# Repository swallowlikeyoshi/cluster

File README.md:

# HEVEN Cluster 펌웨어

**2026 영광 대회 · 계기 클러스터(Instrument Cluster)** — ESP32가 CAN/BLE로 차량 상태(속도·전압·SOC·온도·에러)를 **받아서** LCD에 표현하고, 계기판 버튼 입력을 VCU로 보냅니다. VESS 신호 경로와 스위칭은 클러스터 ESP32 GPIO 입력에서 분리합니다. VCU와 달리 **안전 임계가 약한 표시 전용 보드**입니다.

> 🤖 **AI 에이전트/팀원은 [`AGENTS.md`](AGENTS.md)를 먼저 읽으세요** — 무엇을 고쳐도 되고 무엇을 건드리면 안 되는지 규칙이 있습니다.

---

## 한눈에

- **스택**: PlatformIO + Arduino-ESP32, TWAI(CAN), ILI9341 LCD. 화면은 **패널 독립적 1bpp 프레임버퍼**(위젯이 그림) + `display_blit`(ILI9341로 blit)
- **구조**: 잠긴 코어(CAN·프레임버퍼·blit) + 팀원이 채우는 순수 모듈(`src/modules/`). VCU와 **동일한 2층 설계**지만 안전 FSM·50ms 라이프 태스크가 없고 CAN은 **수신(RX) 위주**입니다.
- **상태**: ESP32 빌드 그린, 호스트 테스트 39개 통과

## 빠른 시작

```bash
# 1. 이 레포를 깨끗한 위치에 클론
git clone https://github.com/2026-HEVEN/cluster.git
cd cluster

# 2. PlatformIO 설치 (한 번만) — VS Code면 PlatformIO IDE 확장 설치로 대체 가능
uv tool install platformio      # 또는: pipx install platformio

# 3. 노트북에서 테스트 (하드웨어 불필요)
pio test -e native

# 4. 보드에 빌드 & 업로드 (ESP32 연결 상태에서)
pio run -e esp32dev -t upload
```

> 🧪 **테스트가 처음이거나 Windows 사용자라면** → 노션 [펌웨어 테스트 실행 방법](https://www.notion.so/390913e532e68199a9b5e340b73e9e71) 참고. AI에 복붙할 프롬프트 + "이렇게 나오면 성공" 출력 예시 + Windows(WSL2/MinGW) 셋업까지 있습니다. (보드 업로드는 Windows도 그냥 되고, `native` 단위테스트만 host 컴파일러가 필요해요.)

> ℹ️ 모터컨트롤러 값은 MCU→VCU 피드백 프레임을 Cluster가 같은 CAN 버스에서 수신합니다. BMS SOC는 `LWS-1608` BLE BMS에 Cluster ESP32가 직접 연결해 표시용 telemetry로만 읽습니다.

## 어디서 작업하나

| 폴더 | 내용 | 편집? |
|------|------|-------|
| `src/modules/` | 순수 계산 함수 `xxx_compute()` | ✅ **여기서만** |
| `test/` | 노트북 단위 테스트 | ✅ |
| `src/core/`, `src/logic/`, `include/` | CAN·framebuffer·display_blit·스케줄러·타입 | 🔒 잠김 |
| `platformio.ini`, `src/main.cpp` | 빌드 설정·진입점 | 🔒 잠김 |

새 모듈을 추가하거나 기존 `compute()`를 채우는 법 → [`docs/ADDING_A_MODULE.md`](docs/ADDING_A_MODULE.md)

## 모듈 목록 (FILL-IN)

- `hmi_input` — config 스위치(패독·TC·회생·디버그) → `ClusterCommand` (CAN으로 VCU에 전송)
- `widgets/` — 계기판 화면 위젯 (speed·battery·warnings·gear ...). 1bpp 프레임버퍼에 그림.
  새 위젯 추가법: `docs/ADDING_A_WIDGET.md`

> 표시는 패널 독립적 **1bpp 프레임버퍼**로. 실제 패널 blit(`display_blit`)은 하드웨어 확정 후 구현.

## 문서

| 문서 | 내용 |
|------|------|
| [`AGENTS.md`](AGENTS.md) / `CLAUDE.md` | 작업 규칙 (에이전트·팀원 필독) |
| [`docs/ADDING_A_MODULE.md`](docs/ADDING_A_MODULE.md) | 모듈 추가/작성 절차 |
| [`docs/CAN_PROTOCOL.md`](docs/CAN_PROTOCOL.md) | CAN 메시지 명세 (VCU/Cluster 공유 단일 출처) |

> 전체 설계 원리(compute/update 분리, state 격리, 테스트 등)는 **VCU 레포의 [`ARCHITECTURE.md`](https://github.com/2026-HEVEN/vcu/blob/main/docs/ARCHITECTURE.md)** 와 동일합니다.

## 아직 미구현 (의도된 TODO)

- **VCU 표시 상태 프레임 구현** — VCU가 `0x1801C0D0`으로 확정 기어/HV/브레이크 상태를 보내면 Cluster가 그 값을 우선 표시합니다.
- **BMS BLE 실차 검증** — `LWS-1608` BLE 이름, `FFE0/FFE1/FFE2` 특성, SOC/current 부호를 실제 배터리팩에서 확인해야 합니다.

## 버전 기록 (Changelog)

> 각 버전은 git 태그로도 관리됩니다 → [GitHub Releases](https://github.com/2026-HEVEN/cluster/releases)
> **새 버전 올릴 때:** 아래에 항목 추가 → `git tag vX.Y` → `git push origin vX.Y`.

### v1.1.1 (2026-07-06) — 위젯 레이아웃 렌더 테스트
- `test/test_render_layout`: `app_wiring.cpp`의 위젯 배치를 그대로 재현해 24bit BMP로 덤프하는 시각화 테스트 추가. `pio test -e native -f test_render_layout` 로 실행 → `render_layout.bmp` 생성(Windows 사진 앱/그림판 등 추가 도구 없이 바로 열림), 위젯별 할당 공간을 박스로 표시
- `.gitignore`에 `*.bmp` 추가

### v1.1 (2026-06-29) — 디스플레이 프레임버퍼 재설계
- 패널 독립적 **1bpp 프레임버퍼**(320×160) + 위젯 모듈(speed · battery · warnings · gear) 도입 — 렌더링을 모듈로 넘겨 자유도↑, host 테스트 가능(ASCII 시각화)
- `hmi_input` → **`ClusterCommand`**(paddock · TC · regen · debug) 의미 커맨드 패턴, **패독 모드** 추가
- **제거**: `vess`, `indicators`, `display_render`(U8g2), `io_expander`(MCP23017)
- `display_blit` stub(패널 확정 후 구현), CAN 커맨드 레이아웃(`CAN_PROTOCOL.md` §5.7) 갱신

### v1.0 (2026-06-29) — 초기 Cluster 펌웨어 베이스
- 잠긴 코어(CAN RX · MCP23017 · U8g2 OLED) + 순수 모듈(display · indicators · vess · hmi_input)
- PlatformIO native 테스트, AGENTS/ADDING_A_MODULE/CAN_PROTOCOL 문서

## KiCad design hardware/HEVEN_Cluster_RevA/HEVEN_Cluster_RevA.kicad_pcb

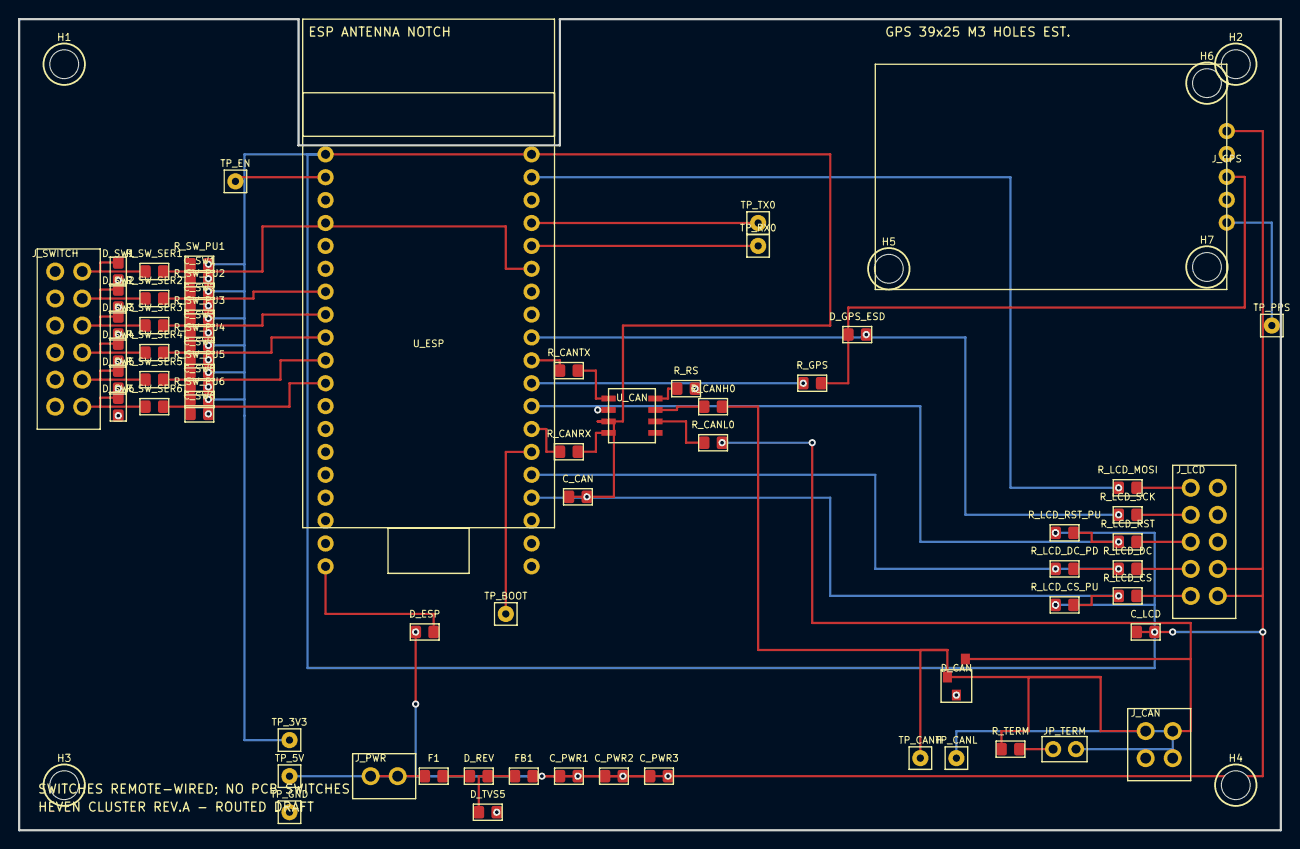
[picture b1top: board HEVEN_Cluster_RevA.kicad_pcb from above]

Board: 2 copper layers, 140.0 x 90.0 mm, 76 parts (0 on the bottom side), 46 nets.

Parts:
C_CAN: 100nF; C_CAN
C_LCD: 10uF; C_LCD
C_PWR1: 100uF; C_PWR1
C_PWR2: 10uF; C_PWR2
C_PWR3: 100nF; C_PWR3
C_SW1: 100nF; C_SW1
C_SW2: 100nF; C_SW2
C_SW3: 100nF; C_SW3
C_SW4: 100nF; C_SW4
C_SW5: 100nF; C_SW5
C_SW6: 100nF; C_SW6
D_CAN: PESD1CAN; D_CAN
D_ESP: SS34; D_ESP
D_GPS_ESD: PESD3V3; D_GPS_ESD
D_REV: SS34; D_REV
D_SW1: PESD3V3; D_SW1
D_SW2: PESD3V3; D_SW2
D_SW3: PESD3V3; D_SW3
D_SW4: PESD3V3; D_SW4
D_SW5: PESD3V3; D_SW5
D_SW6: PESD3V3; D_SW6
D_TVS5: SMBJ5.0A; D_TVS5
F1: PTC 1.1A; F1
FB1: Ferrite 600R; FB1
H1, H2, H3, H4: M3_MAIN; MountingHole
H5, H6, H7: M3_GPS_EST; MountingHole
JP_TERM: 120R ENABLE; JP_TERM
J_CAN: Molex 43045-0412 CAN; J_CAN
J_GPS: SZH-NEO03 1x5 RA socket; J_GPS
J_LCD: Molex 43045-1012, LCD cable; J_LCD
J_PWR: Molex 43045-0212 regulated 5V input; J_PWR
J_SWITCH: Molex 43045-1212, 6 signal/GND pairs; J_SWITCH
R_CANH0: 0R; R_CANH0
R_CANL0: 0R; R_CANL0
R_CANRX: 33R; R_CANRX
R_CANTX: 33R; R_CANTX
R_GPS: 1k; R_GPS
R_LCD_CS: 33R; R_LCD_CS
R_LCD_CS_PU: 10k; R_LCD_CS_PU
R_LCD_DC: 33R; R_LCD_DC
R_LCD_DC_PD: 100k; R_LCD_DC_PD
R_LCD_MOSI: 33R; R_LCD_MOSI
R_LCD_RST: 33R; R_LCD_RST
R_LCD_RST_PU: 10k; R_LCD_RST_PU
R_LCD_SCK: 33R; R_LCD_SCK
R_RS: 10k; R_RS
R_SW_PU1: 10k; R_SW_PU1
R_SW_PU2: 10k; R_SW_PU2
R_SW_PU3: 10k; R_SW_PU3
R_SW_PU4: 10k; R_SW_PU4
R_SW_PU5: 10k; R_SW_PU5
R_SW_PU6: 10k; R_SW_PU6
R_SW_SER1: 1k; R_SW_SER1
R_SW_SER2: 1k; R_SW_SER2
R_SW_SER3: 1k; R_SW_SER3
R_SW_SER4: 1k; R_SW_SER4
R_SW_SER5: 1k; R_SW_SER5
R_SW_SER6: 1k; R_SW_SER6
R_TERM: 120R; R_TERM
TP_3V3: TP; TP_3V3
TP_5V: TP; TP_5V
TP_BOOT: TP; TP_BOOT
TP_CANH: TP; TP_CANH
TP_CANL: TP; TP_CANL
TP_EN: TP; TP_EN
TP_GND: TP; TP_GND
TP_PPS: TP; TP_PPS
TP_RX0: TP; TP_RX0
TP_TX0: TP; TP_TX0
U_CAN: SN65HVD230D; U_CAN
U_ESP: YD-ESP32 USB-C Core Board; U_ESP

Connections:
3V3: C_CAN.1, R_LCD_CS_PU.1, R_LCD_RST_PU.1, R_SW_PU1.2, R_SW_PU2.2, R_SW_PU3.2, R_SW_PU4.2, R_SW_PU5.2, R_SW_PU6.2, TP_3V3.1, U_CAN.3, U_ESP.1
5V_FUSED: D_REV.1, F1.2
5V_IN: F1.1, J_PWR.1
5V_PROT: D_REV.2, D_TVS5.1, FB1.1
5V_SYS: C_LCD.1, C_PWR1.1, C_PWR2.1, C_PWR3.1, D_ESP.1, FB1.2, J_GPS.1, J_LCD.8, J_LCD.10, TP_5V.1
CAN_H: D_CAN.1, J_CAN.1, R_CANH0.2, R_TERM.1, TP_CANH.1
CAN_H_INT: R_CANH0.1, U_CAN.7
CAN_L: D_CAN.3, JP_TERM.2, J_CAN.2, R_CANL0.2, TP_CANL.1
CAN_L_INT: R_CANL0.1, U_CAN.6
CAN_RS: R_RS.1, U_CAN.8
CAN_RX_IC: R_CANRX.2, U_CAN.4
CAN_RX_MCU: R_CANRX.1, U_ESP.32
CAN_TX_IC: R_CANTX.2, U_CAN.1
CAN_TX_MCU: R_CANTX.1, U_ESP.29
ESP_BOOT: TP_BOOT.1, U_ESP.33
ESP_EN: TP_EN.1, U_ESP.2
ESP_VIN: D_ESP.2, U_ESP.19
GND: C_CAN.2, C_LCD.2, C_PWR1.2, C_PWR2.2, C_PWR3.2, C_SW1.2, C_SW2.2, C_SW3.2, C_SW4.2, C_SW5.2, C_SW6.2, D_CAN.2, D_GPS_ESD.2, D_SW1.2, D_SW2.2, D_SW3.2, D_SW4.2, D_SW5.2, D_SW6.2, D_TVS5.2, J_CAN.3, J_GPS.2, J_LCD.2, J_LCD.4, J_LCD.6, J_PWR.2, J_SWITCH.2, J_SWITCH.4, J_SWITCH.6, J_SWITCH.8, J_SWITCH.10, J_SWITCH.12, R_LCD_DC_PD.1, R_RS.2, TP_GND.1, U_CAN.2, U_ESP.14, U_ESP.20, U_ESP.26
GPS_PPS: J_GPS.5, TP_PPS.1
GPS_RX_MCU: R_GPS.1, U_ESP.30
GPS_TX_RAW: D_GPS_ESD.1, J_GPS.3, R_GPS.2
LCD_CS: J_LCD.9, R_LCD_CS.2
LCD_CS_MCU: R_LCD_CS.1, R_LCD_CS_PU.2, U_ESP.35
LCD_DC: J_LCD.7, R_LCD_DC.2
LCD_DC_MCU: R_LCD_DC.1, R_LCD_DC_PD.2, U_ESP.34
LCD_MOSI: J_LCD.1, R_LCD_MOSI.2
LCD_MOSI_MCU: R_LCD_MOSI.1, U_ESP.21
LCD_RST: J_LCD.5, R_LCD_RST.2
LCD_RST_MCU: R_LCD_RST.1, R_LCD_RST_PU.2, U_ESP.31
LCD_SCK: J_LCD.3, R_LCD_SCK.2
LCD_SCK_MCU: R_LCD_SCK.1, U_ESP.28
SW_GEAR_D_MCU: C_SW3.1, R_SW_PU3.1, R_SW_SER3.2, U_ESP.8
SW_GEAR_D_RAW: D_SW3.1, J_SWITCH.5, R_SW_SER3.1
SW_GEAR_R_MCU: C_SW2.1, R_SW_PU2.1, R_SW_SER2.2, U_ESP.7
SW_GEAR_R_RAW: D_SW2.1, J_SWITCH.3, R_SW_SER2.1
SW_LCD_ACTION_MCU: C_SW6.1, R_SW_PU6.1, R_SW_SER6.2, U_ESP.11
SW_LCD_ACTION_RAW: D_SW6.1, J_SWITCH.11, R_SW_SER6.1
SW_PADDOCK_MCU: C_SW5.1, R_SW_PU5.1, R_SW_SER5.2, U_ESP.10
SW_PADDOCK_RAW: D_SW5.1, J_SWITCH.9, R_SW_SER5.1
SW_STATUS_MCU: C_SW1.1, R_SW_PU1.1, R_SW_SER1.2, U_ESP.25
SW_STATUS_RAW: D_SW1.1, J_SWITCH.1, R_SW_SER1.1
SW_VESS_MCU: C_SW4.1, R_SW_PU4.1, R_SW_SER4.2, U_ESP.9
SW_VESS_RAW: D_SW4.1, J_SWITCH.7, R_SW_SER4.1
TERM_NODE: JP_TERM.1, R_TERM.2
UART0_RX: TP_RX0.1, U_ESP.24
UART0_TX: TP_TX0.1, U_ESP.23

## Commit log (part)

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2026-06-30 chore(cluster): scaffold PlatformIO project + agent guidance
2026-06-30 feat(cluster): copy shared types + scheduler from VCU
2026-06-30 feat(cluster): CAN protocol base + feedback/cmd IDs + decoders
2026-06-30 feat(cluster): ClusterState shared bus
2026-06-30 feat(cluster): indicators module (faults -> lamp bitmask)
2026-06-30 feat(cluster): vess module (speed -> simple tone)
2026-06-30 feat(cluster): display module (pure view model)
2026-06-30 feat(cluster): MCP23017 io_expander driver (locked)
2026-06-30 feat(cluster): U8g2 OLED renderer (locked)
2026-06-30 feat(cluster): TWAI CAN core (RX stub + command TX, no life task)
2026-06-30 feat(cluster): app wiring + entry point; full ESP32 build green
2026-06-30 docs(cluster): how-to guide for adding a module
